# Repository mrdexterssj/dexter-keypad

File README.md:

# Dexter keypad

This is a custom keypad built based on Half Life's Week 3 starter project by [KaiPereira](https://github.com/KaiPereira), with some edits by me!

## Overview

This keypad uses Capacitive Keys, which are exposed copper pads that catch your electrostatic energy and send a signal to special pins in your microcontroller. The keypad has 7 keys and uses the Waveform ESP32-S3-Zero. 

It also includes 3 switches for custom functionality and a rotary encoder (potentiometer) with a built-in click functionality. Finally, it includes 3 SK6812MINI-E LEDs for RGB or regular lightning.

## Features

* MIDI output through USB-C (pending)
* MicroPython firmware (basic [template](https://github.com/KMKfw/kmk_firmware/blob/main/docs/en/Getting_Started.md))
* Programmable LEDs
* 3 switches for extra functionality
* 4 M3 3.2mm mounting holes
* Potentiometer with built-in switch for extra functionality

## Button layout
* Button 1: set mode to minor notes
* Button 2: set mode to flat (bemols) notes
* Button 3: set mode to sharp notes
* Potentiometer switch: reset to normal mode (major notes)

Button 1, 2 and 3 have their respective LEDs, which will turn on when they are clicked. Only one may turn on at the same time.

NOTE: this is planned to be added as firmware in the build weeks, so I can safely flash and test the firmware as no template firmware was provided

## BOM Table
|Item                                          |Qty|Supplier   |Cost/item|Total Cost|link                                                                                                                                          |Note                                                       |
|----------------------------------------------|---|-----------|---------|----------|----------------------------------------------------------------------------------------------------------------------------------------------|-----------------------------------------------------------|
|Waveshare ESP32-S3-Zero                       |1  |Waveshare  |$5.49    |$5.49     |https://www.waveshare.com/esp32-s3-zero.htm?sku=25081                                                                                         |                                                           |
|SK6812MINI-E                                  |3  |Ebee       |$0.0808  |$0.404    |https://www.ebee.com/product-detail/opsco-optoelectronics-sk6812mini-e_620740.html                                                            |                                                           |
|MX Switches               |1  |Temu      |$2.84      |$2.84       |https://www.temu.com/ec/switches-de-teclado-mecanico-intercambiables-para-reemplazo--con-switches-cherry-en---marron-y-negro-g-601099814401749.html?_oak_mp_inf=ENXtpaen1ogBGh1nb29kc19ianN5OXBfc29sZF9vdXRfc2ltaWxhciCkg%2FKwlzQ%3D&top_gallery_url=https%3A%2F%2Fimg.kwcdn.com%2Fproduct%2Ffancy%2F06049d86-3cc3-4781-9007-f4511eb9edf9.jpg&spec_gallery_id=601099814401749&refer_page_sn=10032&freesia_scene=25&_oak_freesia_scene=25&_oak_rec_ext_1=Mjk3&_oak_gallery_order=927050043%2C424683148%2C1200427065%2C1332313479%2C2104336086&refer_page_el_sn=200970&ab_scene=1&refer_page_name=goods&refer_page_id=10032_1792982941107_oiltpbxe8e&_x_sessn_id=jwrfwb0n6x&no_cache_id=gxlv5&is_back=1                                                                            |      |
|RotaryEncoder_Alps_EC11E-Switch_Vertical_H20mm|1  |Temu       |$1.21    |$1.21     |https://www.temu.com/ec/1pc-accesorio-de-robot-s----rotatorio-ec11-potenciometro-digital-para-altavoz-con--5-pines-20mm-g-606209147009488.html|                                                           |
|PCB                                           |1  |Local store|$3.50    |$3.50     |https://novatronicec.com/index.php/product/fabricacion-de-circuitos-impresos-pcb/                                                             |Payment done in person so no shipping costs                |
|                                              |   |           |         |          |                                                                                                                                              |                                                           |
|Estimated total shipping                      |1  |           |         |$20.00    |                                                                                                                                              |                                                           |

## Screenshots

Front render

Back render

PCB Layout

Schematic

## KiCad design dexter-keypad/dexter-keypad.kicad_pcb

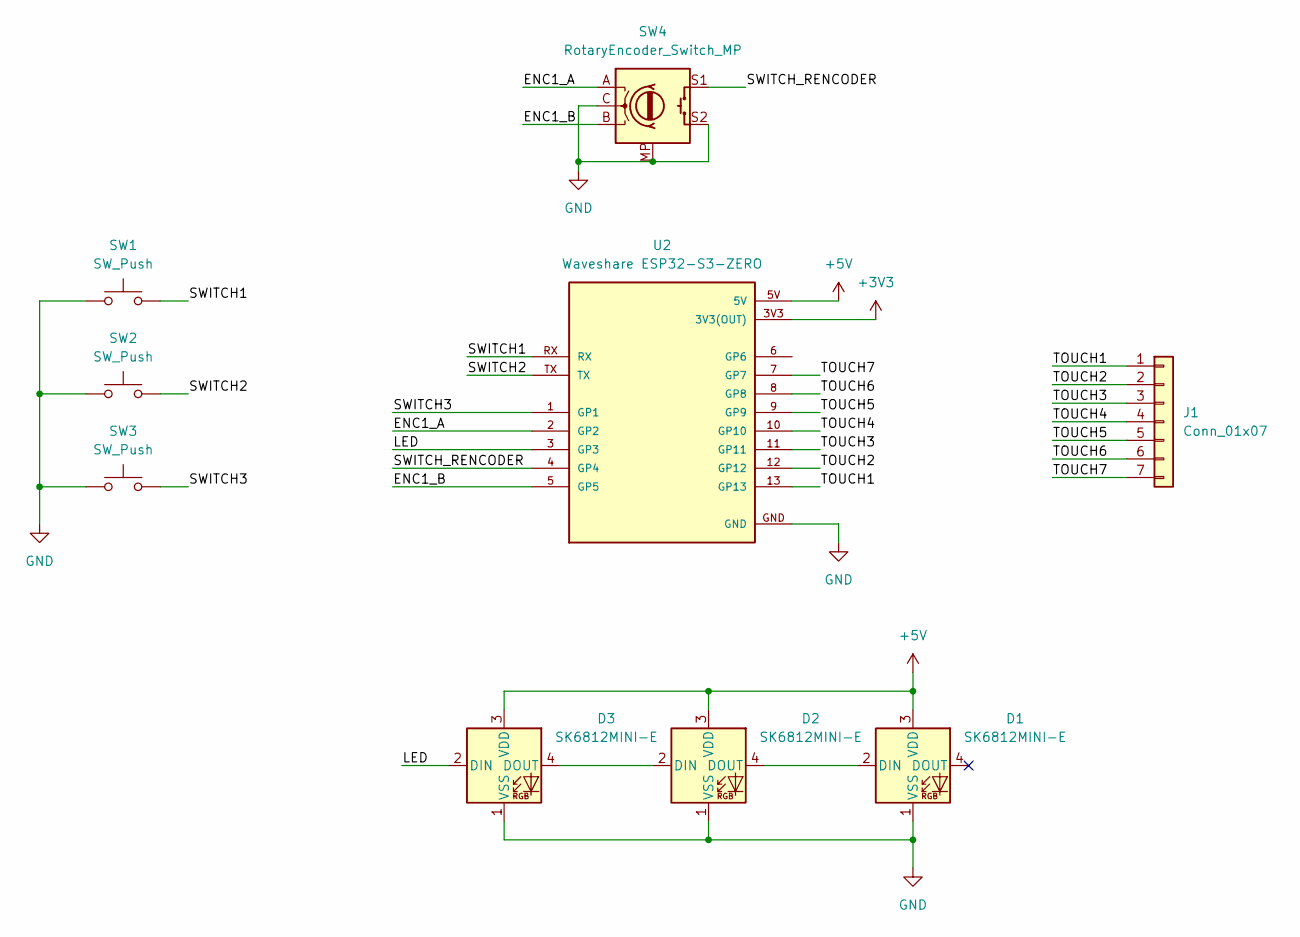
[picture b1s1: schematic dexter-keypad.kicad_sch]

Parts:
D1, D2, D3: SK6812MINI-E; LED_SK6812MINI-E_3.2x2.8mm_P1.5mm_ReverseMount
J1: Conn_01x07; Capacitive_Keys
SW1, SW2, SW3: SW_Push; Kailh Choc Low-Profile Switches
SW4: RotaryEncoder_Switch_MP; RotaryEncoder_Alps_EC11E-Switch_Vertical_H20mm
U2: Waveshare ESP32-S3-ZERO; Waveshare ESP32-S3-Zero; PARTREV NA

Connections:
+3V3: U2.3V3 (3V3(OUT))
+5V: D1.3 (VDD), D2.3 (VDD), D3.3 (VDD), U2.5V
/ENC1_A: SW4.A, U2.2 (GP2)
/ENC1_B: SW4.B, U2.5 (GP5)
/LED: D3.2 (DIN), U2.3 (GP3)
/SWITCH1: SW1.2, U2.RX
/SWITCH2: SW2.2, U2.TX
/SWITCH3: SW3.2, U2.1 (GP1)
/SWITCH_RENCODER: SW4.S1, U2.4 (GP4)
/TOUCH1: J1.1, U2.13 (GP13)
/TOUCH2: J1.2, U2.12 (GP12)
/TOUCH3: J1.3, U2.11 (GP11)
/TOUCH4: J1.4, U2.10 (GP10)
/TOUCH5: J1.5, U2.9 (GP9)
/TOUCH6: J1.6, U2.8 (GP8)
/TOUCH7: J1.7, U2.7 (GP7)
GND: D1.1 (VSS), D2.1 (VSS), D3.1 (VSS), SW1.1, SW2.1, SW3.1, SW4.C, SW4.MP, SW4.S2, U2.GND
unnamed: D1.2 (DIN), D2.4 (DOUT)
unnamed: D2.2 (DIN), D3.4 (DOUT)

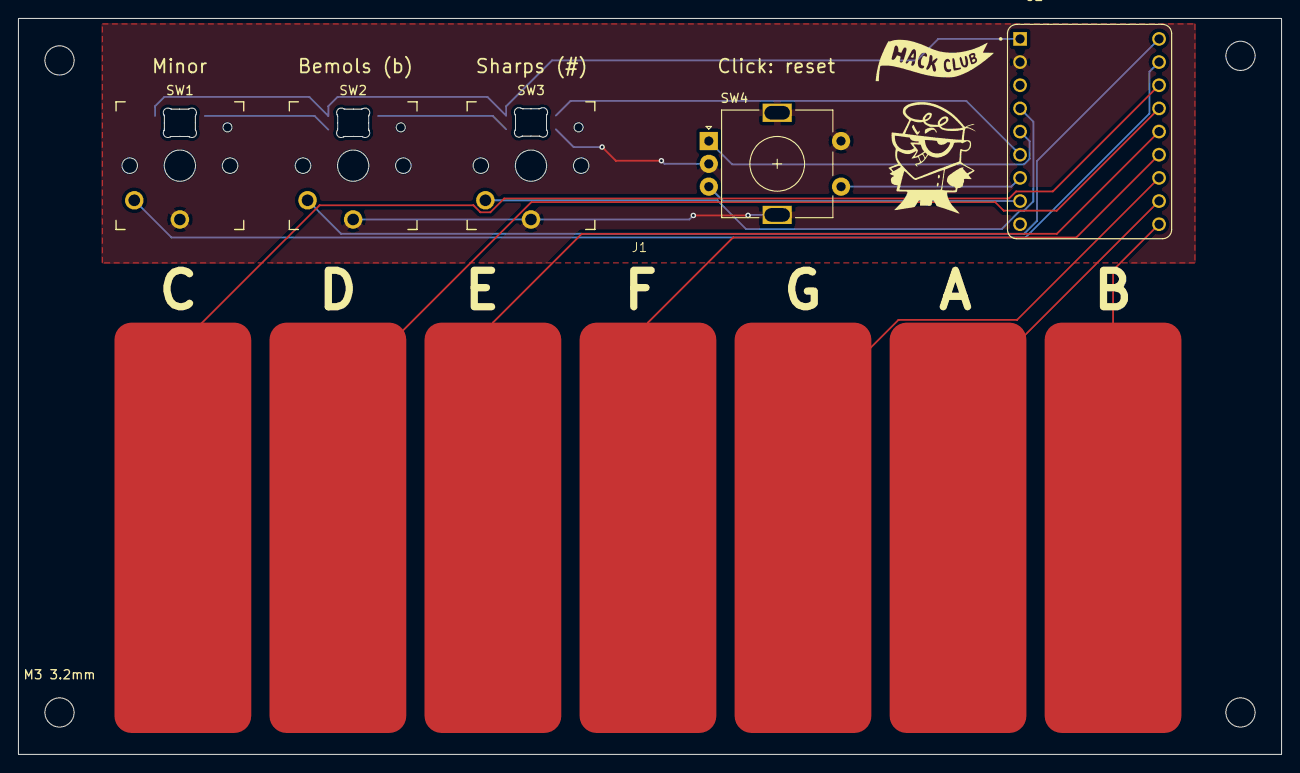
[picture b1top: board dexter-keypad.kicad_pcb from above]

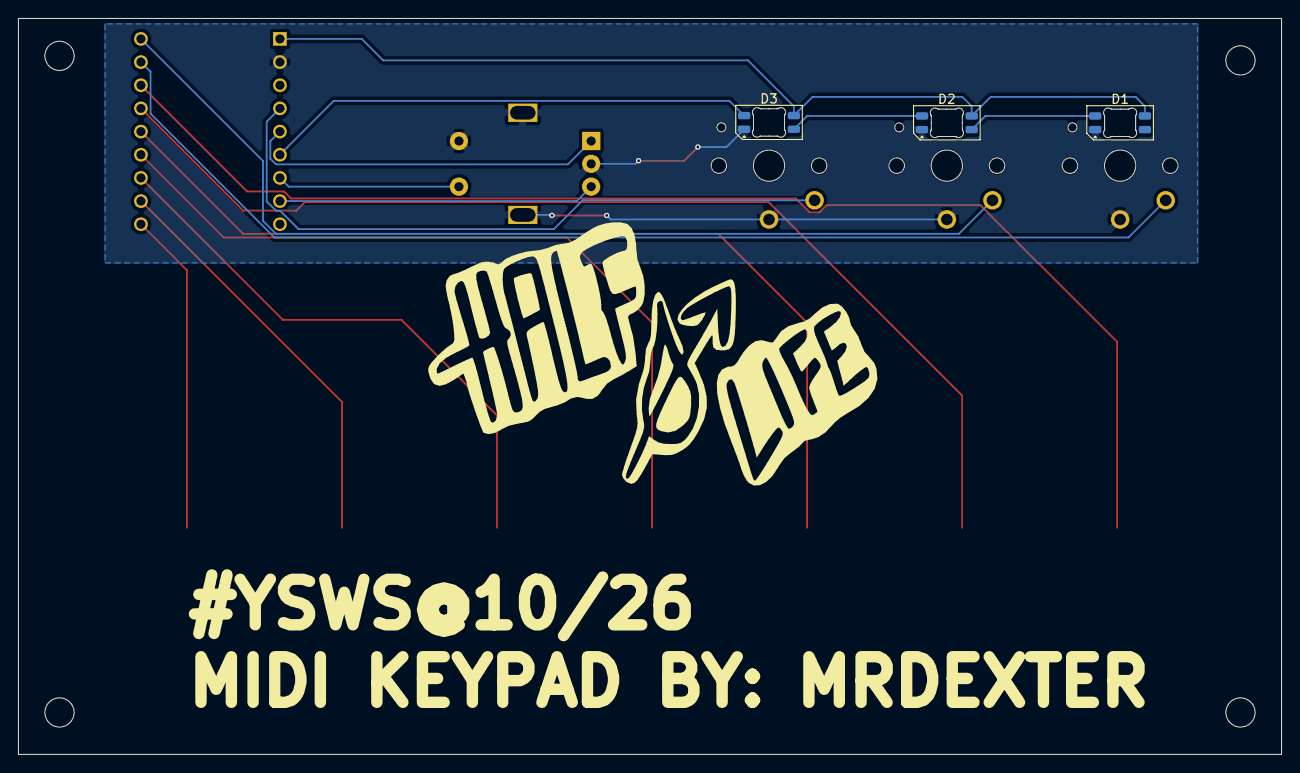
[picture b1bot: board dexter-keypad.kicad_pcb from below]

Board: 2 copper layers, 138.5 x 80.7 mm, 10 parts (3 on the bottom side), 18 nets.

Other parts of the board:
M3 3.2mm: MountingHole_3.2mm_M3
